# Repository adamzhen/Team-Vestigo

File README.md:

# Team-Vestigo

### Crew Tracking for Space Analog Research

Since 2014, NASA’s Johnson Space Center has been using the Human Exploration Research Analog (HERA) to simulate manned space missions on Earth. We are currently developing an upgrade to HERA that will track the location and orientation of crew members in real-time, enabling researchers to efficiently analyze metrics such as how long crew members spent in certain areas or next to other crew members. The challenge is to design a device that not only has sufficient accuracy and battery life, but also a compact size and minimal crew interaction. This project is part of the Texas Space Grant Consortium Design Challenge.

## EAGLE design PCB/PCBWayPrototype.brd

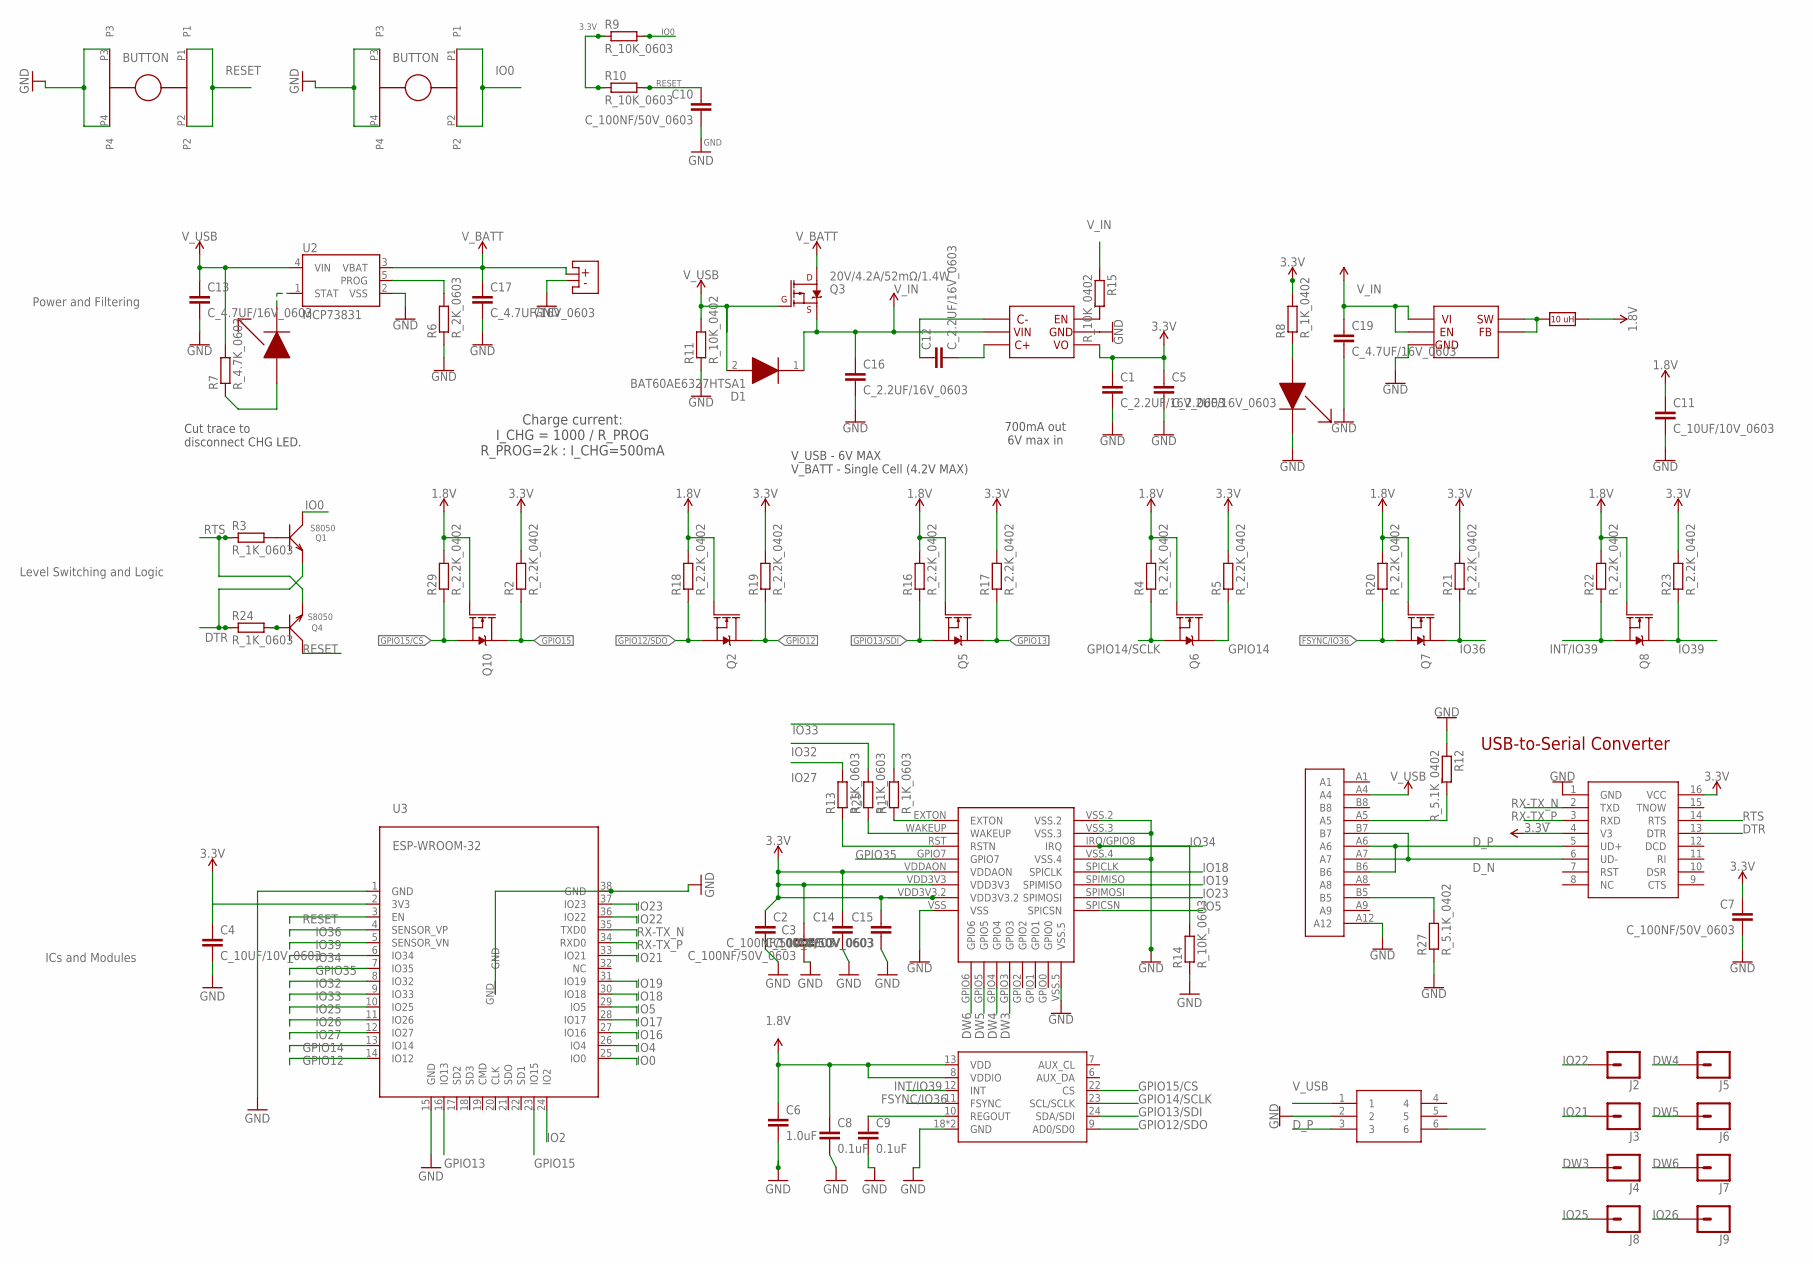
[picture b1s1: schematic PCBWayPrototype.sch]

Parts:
C1, C5, C12, C16: C_2.2UF/16V_0603; C0603
C2, C4, C11: C_10UF/10V_0603; C0603
C3, C7, C10, C14, C15: C_100NF/50V_0603; C0603
C6: 1.0uF; 0603
C8, C9: 0.1uF; 0603
C13, C17, C19: C_4.7UF/16V_0603; C0603
D1: BAT60AE6327HTSA1; SOD2513X110N
J2, J3, J4, J5, J6, J7, J8, J9: CONN_01PTH_2MM; 1X01_2MM
Q1, Q4: S8050; SOT23
Q2, Q5, Q6, Q7, Q8, Q10: 20V/0.2A/8MHz/1.2Ω/1Vth; SOT-416FL
Q3: 20V/4.2A/52mΩ/1.4W; SOT23-3@1
R1, R3, R13, R24, R25: R_1K_0603; R0603
R2, R4, R5, R16, R17, R18, R19, R20, R21, R22, R23, R29: R_2.2K_0402; R0402
R6: R_2K_0603; R0603
R7: R_4.7K_0603; R0603
R8: R_1K_0402; R0402
R9, R10, R14: R_10K_0603; R0603
R11, R15: R_10K_0402; R0402
R12, R27: R_5.1K_0402; R0402
U2: MCP73831; SOT23-5
U3: ESP-WROOM-32
U5: DWM1000
U$1, U$3: K2-6639SP-C4SC-04_C83206; K2-6639SP-C4SC-04
U$2: MLF2012
U$4: TPS62202DBVR
U$5: HE9008M6R
U$6, U$9: 19-217/GHC-YR1S2/3T
U$7: TPSMF05CT1G
U$8: SM02B_PASS_TB_LF
U$10: USBC19
U$11: CH340B; SOP-16
U$12: ICM20948

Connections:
1.8V: C6.1, C8.1, C11.1, Q2.1 (G), Q5.1 (G), Q6.1 (G), Q7.1 (G), Q8.1 (G), Q10.1 (G), R4.2, R16.2, R18.2, R20.2, R22.2, R29.2, U$2.2, U$12.8 (VDDIO), U$12.13 (VDD)
3.3V: C1.1, C2.1, C3.1, C4.1, C5.1, C7.1, C14.1, C15.1, R2.2, R5.2, R8.2, R9.1, R10.1, R17.2, R19.2, R21.2, R23.2, U3.2 (3V3), U5.VDD3V3, U5.VDD3V3.2, U5.VDDAON, U$5.VOUT (VO), U$11.4 (V3), U$11.16 (VCC)
CHG_LED: R7.1, U$6.2 (1)
DTR: Q1.2 (E), R24.1, U$11.13 (DTR)
DW3: J4.1, U5.GPIO3
DW4: J5.1, U5.GPIO4
DW5: J6.1, U5.GPIO5
DW6: J7.1, U5.GPIO6
D_N: U$7.6, U$10.A7, U$10.B7, U$11.6 (UD-)
D_P: U$7.3, U$10.A6, U$10.B6, U$11.5 (UD+)
FSYNC/IO36: Q7.2 (S), R20.1, U$12.11 (FSYNC)
GND: C1.2, C2.2, C3.2, C4.2, C5.2, C6.2, C7.2, C8.2, C9.2, C10.2, C11.2, C13.2, C14.2, C15.2, C16.2, C17.2, C19.2, R6.1, R11.1, R12.1, R14.1, R27.1, U2.2 (VSS), U3.1 (GND), U3.15 (GND), U3.38 (GND), U3.GND, U5.VSS, U5.VSS.2, U5.VSS.3, U5.VSS.4, U5.VSS.5, U$1.P3, U$1.P4, U$3.P3, U$3.P4, U$4.2 (GND), U$5.GND, U$7.2, U$8.3 (-), U$9.1 (2), U$10.A12, U$11.1 (GND), U$12.18 (GND), U$12.20 (GND)
GPIO12: Q2.3 (D), R19.1, U3.14 (IO12)
GPIO12/SDO: Q2.2 (S), R18.1, U$12.9 (AD0/SD0)
GPIO13: Q5.3 (D), R17.1, U3.16 (IO13)
GPIO13/SDI: Q5.2 (S), R16.1, U$12.24 (SDA/SDI)
GPIO14: Q6.3 (D), R5.1, U3.13 (IO14)
GPIO14/SCLK: Q6.2 (S), R4.1, U$12.23 (SCL/SCLK)
GPIO15: Q10.3 (D), R2.1, U3.23 (IO15)
GPIO15/CS: Q10.2 (S), R29.1, U$12.22 (CS)
GPIO35: U3.7 (IO35), U5.GPIO7
INT/IO39: Q8.2 (S), R22.1, U$12.12 (INT)
IO0: Q1.3 (C), R9.2, U3.25 (IO0), U$3.P1, U$3.P2
IO2: U3.24 (IO2)
IO4: U3.26 (IO4)
IO5: U3.29 (IO5), U5.SPICSN
IO16: U3.27 (IO16)
IO17: U3.28 (IO17)
IO18: U3.30 (IO18), U5.SPICLK
IO19: U3.31 (IO19), U5.SPIMISO
IO21: J3.1, U3.33 (IO21)
IO22: J2.1, U3.36 (IO22)
IO23: U3.37 (IO23), U5.SPIMOSI
IO25: J8.1, U3.10 (IO25)
IO26: J9.1, U3.11 (IO26)
IO27: R13.2, U3.12 (IO27)
IO32: R25.2, U3.8 (IO32)
IO33: R1.2, U3.9 (IO33)
IO34: R14.2, U3.6 (IO34), U5.IRQ/GPIO8 (IRQ)
IO36: Q7.3 (D), R21.1, U3.4 (SENSOR_VP)
IO39: Q8.3 (D), R23.1, U3.5 (SENSOR_VN)
unnamed: Q4.1 (B), R24.2
unnamed: Q1.1 (B), R3.2
unnamed: R6.2, U2.5 (PROG)
unnamed: R8.1, U$9.2 (1)
unnamed: U2.1 (STAT), U$6.1 (2)
unnamed: U$2.1, U$4.4 (FB), U$4.5 (SW)
unnamed: R15.2, U$5.EN
unnamed: R1.1, U5.EXTON
unnamed: R25.1, U5.WAKEUP
unnamed: R13.1, U5.RST (RSTN)
unnamed: C9.1, U$12.10 (REGOUT)
unnamed: C12.1, U$5.C-
unnamed: C12.2, U$5.C+
unnamed: R27.2, U$10.B5
unnamed: R12.2, U$10.A5
RESET: C10.1, Q4.3 (C), R10.2, U3.3 (EN), U$1.P1, U$1.P2
RTS: Q4.2 (E), R3.1, U$11.14 (RTS)
RX-TX_N: U3.35 (TXD0), U$11.2 (TXD)
RX-TX_P: U3.34 (RXD0), U$11.3 (RXD)
V_BATT: C17.1, Q3.3 (D), U2.3 (VBAT), U$8.4 (+)
V_IN: C16.1, C19.1, D1.1 (K), Q3.2 (S), R15.1, U$4.1 (VI), U$4.3 (EN), U$5.VIN
V_USB: C13.1, D1.2 (A), Q3.1 (G), R7.2, R11.2, U2.4 (VIN), U$7.1, U$10.A4

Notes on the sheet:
USB-to-Serial Converter
700mA out 6V max in
V_USB - 6V MAX V_BATT - Single Cell (4.2V MAX)
Charge current: I_CHG = 1000 / R_PROG R_PROG=2k : I_CHG=500mA
Cut trace to disconnect CHG LED.
Power and Filtering
Level Switching and Logic
ICs and Modules

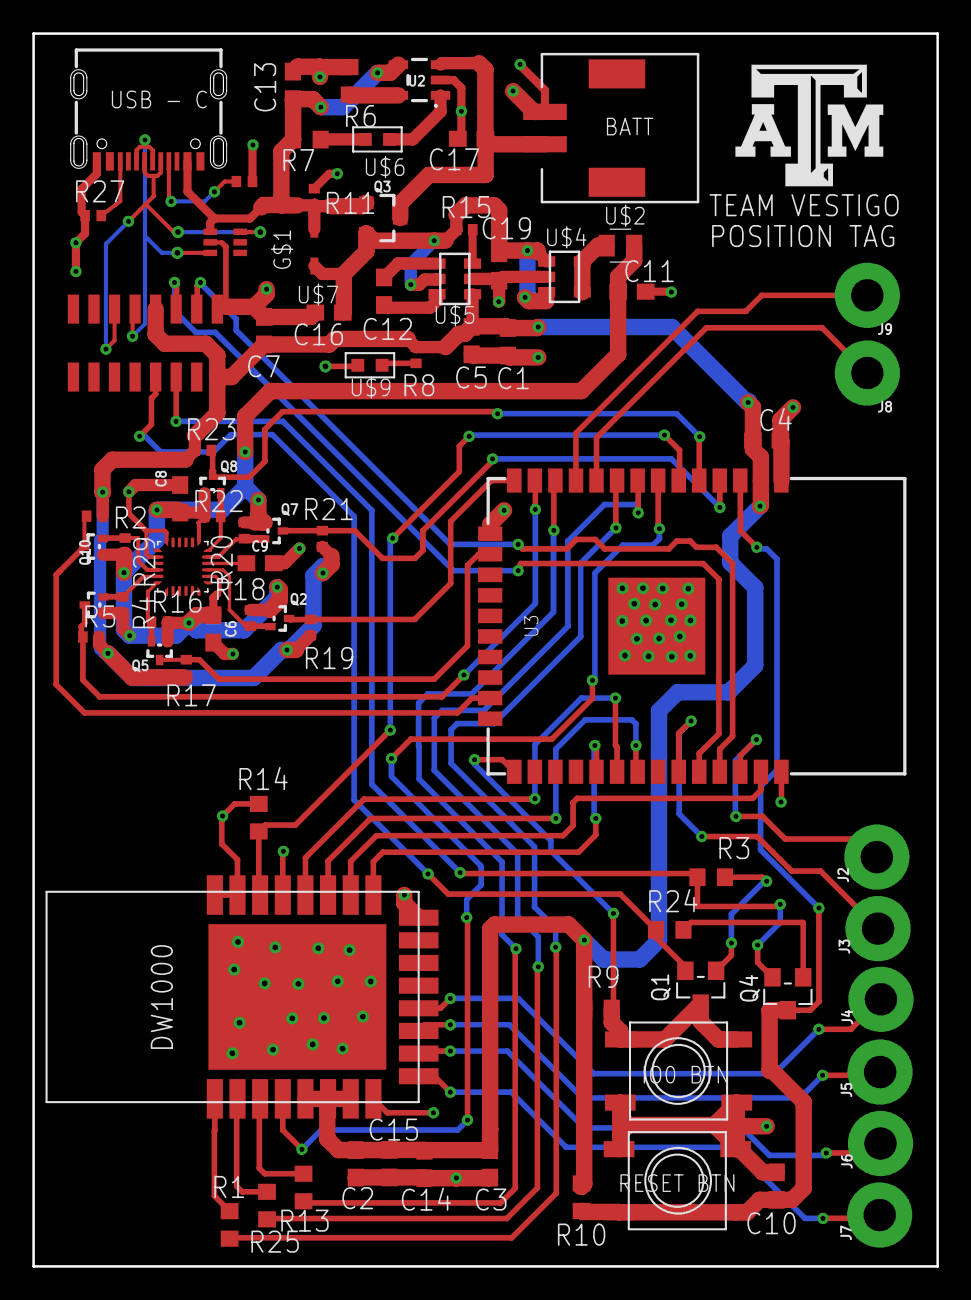
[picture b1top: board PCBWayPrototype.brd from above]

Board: 4 copper layers, 55.9 x 76.2 mm, 78 parts (0 on the bottom side), 59 nets.

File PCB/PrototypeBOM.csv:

Part,Value,Device,Package,Description,IOUT,PROD_ID,SF_ID,VALUE,VOUT,
C1,1.0uF,1.0UF-0402T-16V-10%,0402-TIGHT,1µF ceramic capacitors,,CAP-12417,,1.0uF,,
C2,0.1uF,0.1UF-0402T-6.3V-10%-X7R,0402-TIGHT,0.1µF ceramic capacitors,,CAP-14993,,0.1uF,,
C3,0.1uF,C-0603,C0603,Ceramic Capacitors,,,,,,
C4,1.0uF,1.0UF-0603-16V-10%-X7R,0603,1µF ceramic capacitors,,CAP-13930,,1.0uF,,
C5,10uF,10UF-0402T-6.3V-20%,0402-TIGHT,10.0µF ceramic capacitors,,CAP-14848,,10uF,,
C6,10uF,C-EUC0603,C0603,"CAPACITOR, European symbol",,,,,,
C7,1.0uF,C-0603,C0603,Ceramic Capacitors,,,,,,
C8,10uF,C-0603,C0603,Ceramic Capacitors,,,,,,
C9,0.1uF,C-0603,C0603,Ceramic Capacitors,,,,,,
C10,1.0uF,1.0UF-0402T-16V-10%,0402-TIGHT,1µF ceramic capacitors,,CAP-12417,,1.0uF,,
C11,0.1uF,C-0603,C0603,Ceramic Capacitors,,,,,,
C12,4.7uF,4.7UF-0402_TIGHT-6.3V-20%-X5R,0402-TIGHT,4.7µF ceramic capacitors,,CAP-14240,,4.7uF,,
C13,0.1uF,0.1UF-0402T-6.3V-10%-X7R,0402-TIGHT,0.1µF ceramic capacitors,,CAP-14993,,0.1uF,,
C14,0.1uF,C-0603,C0603,Ceramic Capacitors,,,,,,
C15,0.1uF,C-0603,C0603,Ceramic Capacitors,,,,,,
C19,4.7uF,4.7UF-0603-35V-(20%),0603,4.7µF ceramic capacitors,,CAP-14106,,4.7uF,,
D1,Yellow,LED-YELLOW0603,LED-0603,Yellow SMD LED,,DIO-09003,,Yellow,,
D4,3A/10V/280mV,DIODE-SCHOTTKY-BAT60A,SOD-323,Schottky diode,,DIO-14072,,3A/10V/280mV,,
D12,RED,LED-RED0603,LED-0603,Red SMD LED,,DIO-00819,,RED,,
J1,USB Type C,USB_C_2-LAYER_PADS,USB-C-16P-2LAYER-PADS,USB Type C 16Pin Connector,,CONN-14122,,,,
J3,Connector ,"CONN_10"";1X10""",Multi connection point. Often used as Generic Header-pin footprint for 0.1 inch spaced/style header connections,,CONN-11563,,,,,
J4,Battery Connector,JST_2MM_MALE,JST-2-SMD,JST 2MM MALE RA CONNECTOR,,CONN-11443,PRT-08612,,,
JP2,JUMPER-SMT_2_NC_TRACE_SILK,JUMPER-SMT_2_NC_TRACE_SILK,SMT-JUMPER_2_NC_TRACE_SILK,Normally closed trace jumper,,,,,,
Q1,S8050,TRANSISTOR-NPN-SOT23,SOT23,NPN audion,,,,,,
Q3,20V/4.2A/52m?/1.4W,MOSFET_PCH-DMG2305UX-7,SOT23-3@1,P-channel MOSFETs,,TRANS-14388,,20V/4.2A/52m?/1.4W,,
Q4,S8050,TRANSISTOR-NPN-SOT23,SOT23,NPN audion,,,,,,
Q6,20V/0.2A/8MHz/1.2?/1Vth,MOSFET-NCH-RE1C002UN,SOT-416FL,N-channel MOSFETs,,TRANS_14399,,20V/0.2A/8MHz/1.2?/1Vth,,
Q8,20V/0.2A/8MHz/1.2?/1Vth,MOSFET-NCH-RE1C002UN,SOT-416FL,N-channel MOSFETs,,TRANS_14399,,20V/0.2A/8MHz/1.2?/1Vth,,
Q10,20V/0.2A/8MHz/1.2?/1Vth,MOSFET-NCH-RE1C002UN,SOT-416FL,N-channel MOSFETs,,TRANS_14399,,20V/0.2A/8MHz/1.2?/1Vth,,
Q12,20V/0.2A/8MHz/1.2?/1Vth,MOSFET-NCH-RE1C002UN,SOT-416FL,N-channel MOSFETs,,TRANS_14399,,20V/0.2A/8MHz/1.2?/1Vth,,
Q14,20V/0.2A/8MHz/1.2?/1Vth,MOSFET-NCH-RE1C002UN,SOT-416FL,N-channel MOSFETs,,TRANS_14399,,20V/0.2A/8MHz/1.2?/1Vth,,
Q16,20V/0.2A/8MHz/1.2?/1Vth,MOSFET-NCH-RE1C002UN,SOT-416FL,N-channel MOSFETs,,TRANS_14399,,20V/0.2A/8MHz/1.2?/1Vth,,
R1,1K,RESISTOR_0603_NOOUT,0603-NO,Resistors,,,,,,
R3,1k,1KOHM-0402T-1/16W-1%,0402-TIGHT,1k? resistor,,RES-14342,,1k,,
R4,2.2k,2.2KOHM-0402T-1/16W-1%,0402-TIGHT,2.2k? resistor,,RES-14341,,2.2k,,
R5,2.2k,2.2KOHM-0402T-1/16W-1%,0402-TIGHT,2.2k? resistor,,RES-14341,,2.2k,,
R6,2.0k,2.0KOHM-0603-1/10W-5%,0603,2k? resistor,,RES-08296,,2.0k,,
R7,10k,10KOHM-0402T-1/16W-1%,0402-TIGHT,10k? resistor,,RES-14241,,10k,,
R8,10k,10KOHM-0402T-1/16W-1%,0402-TIGHT,10k? resistor,,RES-14241,,10k,,
R9,5.1k,5.1KOHM-0402T-1/16W-1%,0402-TIGHT,,,RES-14340,,5.1k,,
R10,5.1k,5.1KOHM-0402T-1/16W-1%,0402-TIGHT,,,RES-14340,,5.1k,,
R11,1K,R-0603,0603,,,,,,,
R12,1K,R-0603,0603,,,,,,,
R13,1K,RESISTOR_0603_NOOUT,0603-NO,Resistors,,,,,,
R14,1K,RESISTOR_0603_NOOUT,0603-NO,Resistors,,,,,,
R15,10K,RESISTOR_0603_NOOUT,0603-NO,Resistors,,,,,,
R16,2.2k,2.2KOHM-0402T-1/16W-1%,0402-TIGHT,2.2k? resistor,,RES-14341,,2.2k,,
R17,2.2k,2.2KOHM-0402T-1/16W-1%,0402-TIGHT,2.2k? resistor,,RES-14341,,2.2k,,
R18,2.2k,2.2KOHM-0402T-1/16W-1%,0402-TIGHT,2.2k? resistor,,RES-14341,,2.2k,,
R19,2.2k,2.2KOHM-0402T-1/16W-1%,0402-TIGHT,2.2k? resistor,,RES-14341,,2.2k,,
R20,2.2k,2.2KOHM-0402T-1/16W-1%,0402-TIGHT,2.2k? resistor,,RES-14341,,2.2k,,
R21,2.2k,2.2KOHM-0402T-1/16W-1%,0402-TIGHT,2.2k? resistor,,RES-14341,,2.2k,,
R22,2.2k,2.2KOHM-0402T-1/16W-1%,0402-TIGHT,2.2k? resistor,,RES-14341,,2.2k,,
R23,2.2k,2.2KOHM-0402T-1/16W-1%,0402-TIGHT,2.2k? resistor,,RES-14341,,2.2k,,
R24,2.2k,2.2KOHM-0402T-1/16W-1%,0402-TIGHT,2.2k? resistor,,RES-14341,,2.2k,,
R25,2.2k,2.2KOHM-0402T-1/16W-1%,0402-TIGHT,2.2k? resistor,,RES-14341,,2.2k,,
R34,1k,1KOHM-0402T-1/16W-1%,0402-TIGHT,1k? resistor,,RES-14342,,1k,,
TP1,1.8V,TEST-POINT3,PAD.03X.03,SparkFun Test Points,,,,,,
U1,9DoF IMU,ICM-20948,QFN24-3X3,ICM-20948 9 Degree of Freedom IMU,,IC-14247,,9DoF IMU,,
U2,MCP73831,MCP73831,SOT23-5,"MCP73831T Li-Ion, Li-Pol Controller",,IC-09995,,,,
U3,ESP-WROOM-32,ESP-WROOM-32,ESP-WROOM-32,,,,,,,
U5,DWM1000,DWM1000,DWM1000,,,,,,,
U6,1.8V/100mA,V_REG_SP6214-1.8V,SC70,Voltage Regulator - SP6214,,VREG-08428,,1.8V/100mA,,
U7,CH340C,CH340C,SO016,,,IC-14038,,,,
U8,XC6222B331MR-G,XC6222B331MR-G,SOT23-5,,700mA,VREG-16775,,,3.3V,
,,,,,,,,,,

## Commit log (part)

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2023-04-02 Working on Orientation
    - Creating MatLAB script to read serial port data from IMU and write to text file
    - Currently takes in 1000 readings, and I've created a graph in excel displaying the roll, pitch, and yaw
2023-04-03 Gravity Tests & Patch
    - Uploading data from gravity tests (3 tests, each with gravity in a different axis) as well as our patch
2023-04-05 WiFi Functionality (MQTT & ThingSpeak), LiPo Fuel Gauge
    - Uploaded lipo battery fuel gauge code from the Thing Plus hookup guide
    - Successfully trasmitted data wirelessly from the ESP to ThingSpeak, but it was limited to 1 transmission every 15 sec, so had to figure something else out
    - Tried using MQTT, with HiveMQ and Mosquitto, but haven't quite figure it out yet
2023-04-07 Create Tracking position
2023-04-08 IMU Data Transmission over UDP
    - Got IMU data transfer working over WiFi (using UDP port 1221)
2023-04-10 Gravity & Accelerometer Calibration
    - Figured out formula for calculating gravity components using roll, pitch, and yaw
    - Ran multiple tests to verify data and calibrate accelerometer data
    - Code is more of less ready to run and transmit data (roll, pitch, yaw, ax, ay, az, dt)
2023-04-11 IMU Position Attempt
    - Position data not looking very good so far, will work on calibrating and trying to find ways to improve
2023-04-11 Fixed UWB
    - Tweaked code to make sure UWB still works
    - Improved calibration of IMU accelerometer
2023-04-12 Update main.cpp
    - Still working on Kalman Filter
2023-04-13 Update main.cpp & IMU Code
2023-04-13 File Upload
2023-04-14 UWB working, IMU const drift
2023-04-15 Final cpp code with IMU data reader
2023-04-16 Fixed room data not being properly read
2023-04-17 Create PlayBack Visualization
2023-04-28 Update PlayBack Visualization
2023-04-28 File Change
2023-05-16 Renamed functions
2023-05-17 Removed Unnecessary TDoA attempt
2023-05-17 Slight change to realtime display
2023-05-19 UWB Tag Anchor prio
2023-05-20 Simplified Code Structure
2023-05-20 Cleared old config files
2023-05-23 PCB Information
    Prototype PCB Schematic (just has the CAD for each component right now) as well as data sheet of each component
2023-05-24 API Updated Code
2023-05-24 API Updated Tag
2023-05-25 More efficient switching algorithm
2023-05-26 Cleaned Up Tag, Anchor ; Added Multi Tag
2023-05-26 Multi WIP
2023-05-30 Removed Receiver Mode on Tag
    Begin to develop ESP NOW Comm network.
    10 hz transmission speed
2023-05-30 fixed syntax
2023-05-30 Added ESP-NOW call functions
2023-05-31 WiFi Socket to Gateway Connection
2023-05-31 Test Config of UDP Connection
2023-06-04 PCB Updates
2023-06-07 Added Level Shifting, Updated Power Supply, Finished Connecting Components
    The core schematic is almost done, may need some additional touches for optional functionality. Once this is done, we can proceed to route all the connections (e.g. commit to the board file)
2023-06-19 Added Automatic Reset of Tag Chain after Failure
2023-06-20 Updated data processing from UDP into 2D vector
    - Created DEV_TEST_CODE.ino to simulate a 4x15 matrix being sent through UDP
    - Updated THE_IMU_CODE.ino
    - Successfully processed JSON string from UDP into 2D vector
    - Fixed bug where the function reading saved room files only read in the first 7 anchor points
    - Next step is to use the data within the 2D vector to get position/orientation and visualize it
2023-06-21 Visualized position/orientation of 4 tags using 4x15 matrix data
    - Created simulation of random locations in a cube of side length 200" (DEV_TEST_CODE.ino) and calculated distances to be sent via UDP to C++ script
    - Functioning SDL visualization of calculated locations of 4 tags, in addition to orientation data
2023-06-21 Refactored Repo to Match New Naming Scheme
2023-06-21 Refactored Server folder
2023-06-21 Renamed folder
    Warning: previous change may alter Master IO.ino which is core functionality
2023-06-21 Refactored into Specific Folders
2023-06-21 Update UWB_Tag.ino
    Added firstRun_check function
    Added sendUpdateToPeer function
    Removed unnecessary while in advancedRanging
    Tag now skips non-functional tags, and sends error to Master IO if all other tags fail
2023-06-22 Added Individual Failure Resets
    Master IO checks individual failed tags and resets
    UWB Tag expands sendUpdate function to include checking for other tag failures
    Struct is getting very large, splitting in two pieces might be necessary
2023-06-22 Tag hard resets after reset command received
2023-06-23 Abstracted advancedRanging function into subfunctions
    Compacted counters in addition
2023-06-23 Syntax Updates
2023-06-23 MIO handles Initialization of Network
    Removed firstRun variable and related code from tag
    Added initialization func to MIO
    MIO initializes on setup
2023-06-23 Syntax Changes
    Lessen delay for waitForPacketSent to 1 ms
2023-06-23 Error Handling of Tag Startup Failure
    Added startNetworkSetup func
    Modified checkTagsOnline to handle repeated tag failure
    Errors sent to server on error port as a json
2023-06-23 Resolved Compilation Errors
    Removed extra brace
    Changed Json array to correctly convert
    Defined ETH_PHY_ADDR
    ETH_CLK_MODE set to 0
2023-06-23 Fixed Compilation Errors
    Added counter input to averageDistanceData
    Moved general functions to bottom
2023-06-23 Corrected MIO Mac Address
2023-06-23 Include SPI library
2023-06-23 Added Fake Mac to Test
2023-06-23 Added debug statements
2023-06-24 Fixed sendUpdateToPeer()
    Moved MIO out of macs array for simplicity
    Moved run_ranging flag to networkData struct
    Updated sendUpdateToPeer to resolve extraneous checks
2023-06-24 Resolve Syntax Errors
2023-06-24 PeerNetwork wait for Packet Sent
2023-06-24 Added waitForPacketSent() to StartUp
    Resolved multiple polling of same tag
2023-06-24 Added sendToPeerNetwork Debug Lines
2023-06-24 Adding Packing to Force Correct Data Sizes
2023-06-24 Removed Extra Print Statements
2023-06-24 Changed rangingData Struct to Packed Type
    Matched MIO Struct to Tag Struct
2023-06-24 Syntax Fix
2023-06-24 Fixed All Tags Activation
    Changed waitForPacketSent to return true and false for appropriate conditions
    Changed sendUpdateToPeer to accommodate previous change
2023-06-24 Changed MIOmac to a uint8_t
2023-06-24 Unique Counter Broken
2023-06-24 Removed Abstractions
2023-06-24 Added Debug Function for Keys
2023-06-24 Added while loop to Fix AdvancedRanging()
2023-06-25 Moved packetSent Flag to Catch Errors
2023-06-25 Added Debug for Tag ID on MIO
2023-06-25 Reverse Ack Data Type
2023-06-25 Fix for uint8_t Conversion
2023-06-25 Syntax Update
2023-06-25 FUNCTIONALITY CHECKPOINT
    Ranging on all tags works
    Tag skipping works
    Network initialization works
    MIO JSON formatting works
    TODO
    Reset commands from tags
2023-06-25 Lowered Delays For Timing
2023-06-25 Commented Out Debugs
2023-06-26 Removed Reset Functions
    Easier way is for MIO to self check data rather than tags waste processing time on checking
2023-06-26 Adjusted Delays
2023-06-26 Added Backwards Failure Check
2023-06-26 Syntax and debug info
2023-06-26 New Attempt at Retro Check
2023-06-26 Moved Run Ranging Reset Flag
    Restored General Functionality
2023-06-26 Fixed Wrong Run_ranging Flag Check
2023-06-26 Syntax Updates
    Removed All Print Statements
    Updates pollPreviousTag to function properly
2023-06-27 Check for Pre-Init of Network
2023-06-27 Refactor files
2023-06-27 Created New Dir
2023-07-12 Grouped Schematic
    Components selected, laid out, not routed yet
2023-07-21 Board Almost Finished
    Need to route IO connectors, retouch design rules, clean up connections, etc
2023-07-25 Resolved all DRC violations
2023-08-06 Finalized PCB
2023-08-06 Reciept
2023-08-08 Large Update
    Switched to only use Eigen (much cleaner in most cases)
    Reduced repetitive sections
    Removed socket connection
    Added serial connection
    Improved LMA slightly (more robust SVD)
    Removed redundant code
2023-08-09 Syntax Update
    Added runtime error detection
    Matched baud rate and removed all debug statements
2023-08-09 Added Delimiter to MIO serial.write
    Data correctly received on Server end.
    LMA always returns to 1,1,1
    Pitch, roll, yaw, and dt having issues being set to zero, sometimes displaying non-zero values when cout.
    Memory issues, invalid pointer?
2023-09-17 Visualization Tool Folder
2023-09-18 VS/SDL Update
    - Reinstalled SDL in hopes of fixing error in Visual Studio, unsuccessful so far
2023-09-20 SDL Error Fix
    - Finally figured out why SDL was giving me errors
    - It was literally just missing one line (#undef main)
2023-09-25 Setting up Qt
    - Decided to try switching from SDL to Qt, which apparently has its own IDA (Qt Creator)
    - Wrote a script to generate random data points into a csv
    - Set up a test project inside Qt Creator and got the main.cpp script to successfully read the csv file (had to figure out how to change the working directory)
2023-09-30 Functionality Update
    MIO still needs checking functions for disconnection cases, but otherwise works well with no immediate errors
2023-10-02 Qt Updates
    - Modified plot example script by putting old version of Vestigo C++ code in and having it display IMU orientation to the graph
    - Moved data reading code out from main function and into its own function (readSensorData)
2023-10-06 Folder Rename
    - Renamed Visualization Tool to GUI
2023-10-11 Added timestamps and serial printing
2023-10-11 Print Statements for TWR Mod
2023-10-11 Working time conversion
2023-10-11 Multiple files Attempt 1
2023-10-11 Multi file attempt 2
2023-10-11 Time Offset and Refactor
2023-10-11 time wrap around correction
2023-10-12 Moved UWB Config to UWBOperations files
2023-10-13 ESP-NOW Functions Added
2023-10-14 Sending uint64 Timestamp and Delayed Start
2023-10-16 Basic Kalman Filter
2023-10-16 Added Tag Code First Attempt
2023-10-17 Removed unnecessary comments
2023-10-17 Added MIO (no functionality) and Reset System
2023-10-28 Kalman filter implemented, Compiles
2023-10-28 Added MAC Addresses
2023-10-28 Fixed Master average ToF error
    Error is likely low sample count and random noise in the system.
    Added several checks which should prevent large average ToFs
2023-10-29 Removed Debug
2023-10-30 Improve frequency offset calculation and Correct Sync
    Need to correctly add timestamps together to prevent looping and other related offsets.
    Work on multi tag support
    Work on displaying tag in VS
    Clean up slave code and probably rename it to not slave code
2023-11-04 Time Functions and Simplification
    Added uint64_t overflow and underflow functions for all basic operations
    Removed unnecessary adjustment of uint64 times
    updateTimeOffsets needs to be compacted and moved to the main function.
    Frequency Offset is not properly computed and needs to be moved to Master Anchor in order to work
    Requires updating ESP-NOW to send and receive frequency and phase offset.
    MIO now properly displays TDoA differences in meters by subtracting constant differences between all data points
2023-11-05 Major GUI Update
    - Created vestigo-gui, where the GUI is currently being built
    - Created 3 classes (with corresponding header and cpp files): tagData, mapWidget, and crewMember
    - Currently taking in live data from serial port, calculating position using Root Finder, and displaying it at a frequency around 0.66 Hz (relatively slow)
    - Data is being recorded to an output csv named with MM:DD:YY
2023-11-06 Attempt to Fix Sync and Data send
2023-11-07 Updated Code
2023-11-08 Bypass Serial Port Connection
    - Updated code to not automatically try to connect to serial port upon startup, allowing users to use it without sensors connected
2023-11-12 Skeleton for playback implemented
    Implemented the basics for playback.
2023-11-12 Revert "Skeleton for playback implemented"
    This reverts commit 408a0d7397ac9e3cf8a9f544486c15681b87da3d.
2023-11-12 Revert "Bypass Serial Port Connection"
    This reverts commit fb2a9edea38c8aa1b849ab34f9eefb08589b44d2.
2023-11-13 Summary scene done
    yay, we have summaryscene working now!!!
2023-11-13 starting to recreate playback
    hopefully you see these changes Adam
2023-11-13 Updated Working Code
    - Fixed a few bugs
2023-11-20 updates idk what
2023-12-04 updated code?
    Updates I guess
2025-03-28 Something changed majorly
2025-03-28 Fixed tags

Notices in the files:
parts and their libraries:
SparkFun-DiscreteSemi: Licensing: Creative Commons ShareAlike 4.0 International - https://creativecommons.org/licenses/by-sa/4.0
